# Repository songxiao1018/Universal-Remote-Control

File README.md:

# [Universal-Remote-Control](https://github.com/songxiao1018/Universal-Remote-Control)

本项目基于Arduino nano开发。采用KiCAD编辑器进行编辑

## 文件目录

| 编号 | 文件夹名        | 功能                     | 备注 |
| :--: | :------------: | :----------------------: | :--: |
| 1 | arduino-nano-data | Arduino nano 数据参考文件 |     |
| 2 | keyboard-nano     | KiCad 工程文件 |                |
| 3 | keyboard-code     | Arduino nano 软件程序部分 |  |

## 项目背景

本人在一次与家中长辈的聊天过程中偶然听到他们对于电视机遥控器的不满，他们对电视机遥控器有如下几个需求：

1. 遥控器操作简单，易于记忆。
2. 网络电视调台操作方便。
3. 遥控器按键已于操作，降低防误操作的发生。

本人在观察电视遥控器后也发现了这个问题的存在。因此，本人便想到了通过Arduino nano来实现一个通用遥控器，通过减少遥控器中的部分按键，集成化按键顺序等方法来解决遥控器操作不方便的问题。

## 项目目标

**基本**

- [x] 1. 实现遥控器基本功能。
- [x] 2. 方便老人使用。

**扩展**

- [ ] 3. 充放电自由，无需频繁更换换电池。
- [ ] 4. 小巧轻便，美丽外观。

## 项目进度

2023.01.10  V1.0a敲定成型，发往工厂制作样板

2022.12.28  项目开始

## 联系方式

- QQ：  2289895723
- Email：skyxiaoxiao@yeah.net
- Github：github.com/songxiao1018
- Blog：www.xiaoxiaosky.top

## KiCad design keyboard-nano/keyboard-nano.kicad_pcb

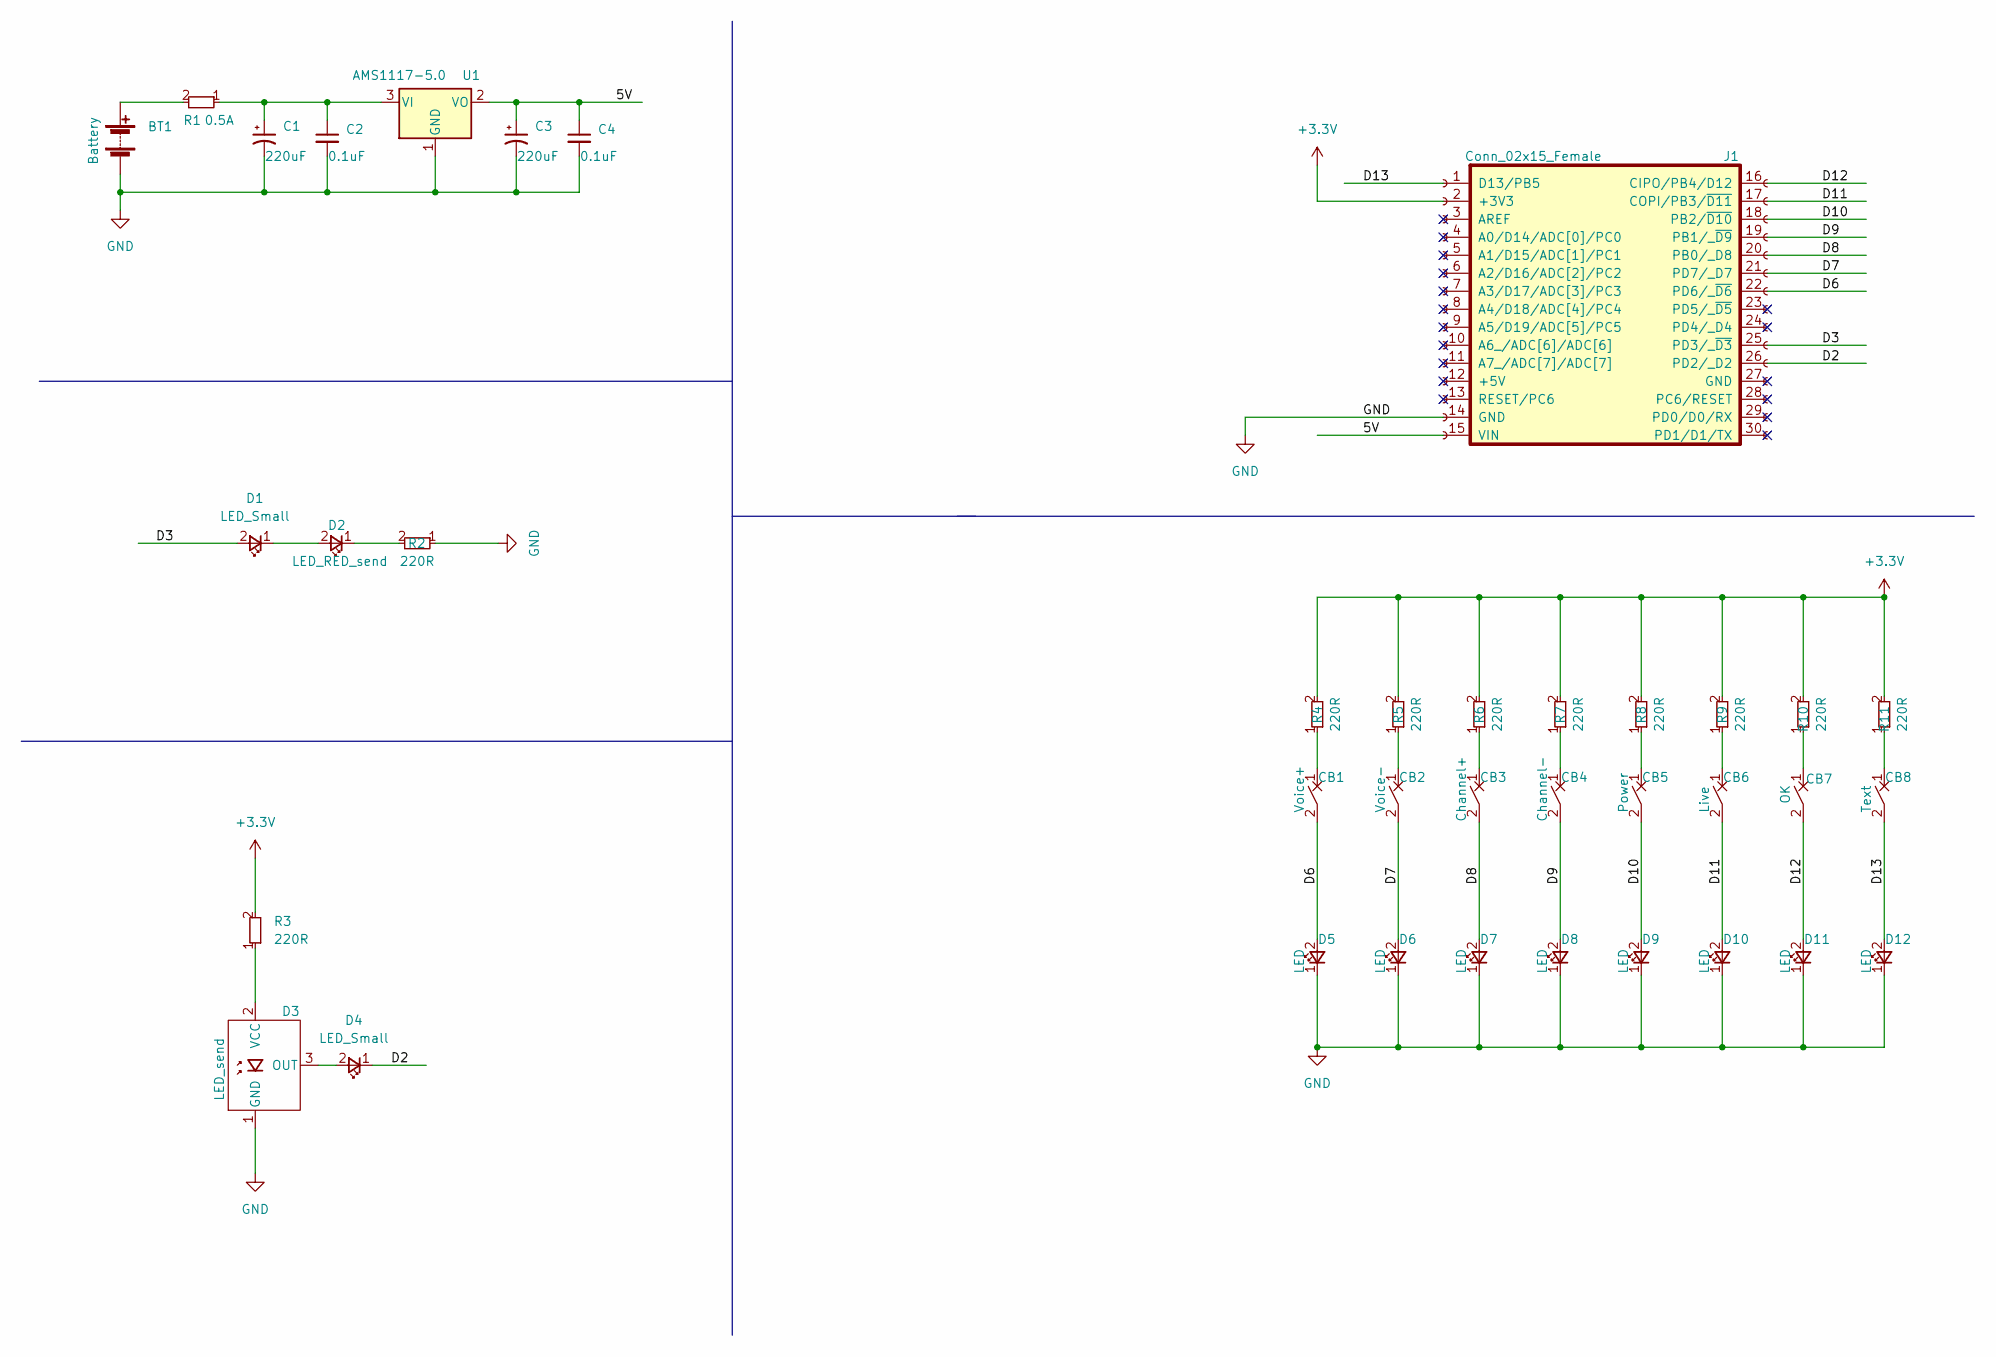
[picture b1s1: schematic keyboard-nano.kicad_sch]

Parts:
BT1: Battery; BatteryHolder_2xAAA_5
C1, C3: 220uF; C_Elec_6.3x7.7
C2, C4: 0.1uF; LED_0805_2012Metric
CB1: Voice+; SW_Cherry_MX_1.00u_Plate
CB2: Voice-; SW_Cherry_MX_1.00u_Plate
CB3: Channel+; SW_Cherry_MX_1.00u_Plate
CB4: Channel-; SW_Cherry_MX_1.00u_Plate
CB5: Power; SW_Cherry_MX_1.00u_Plate
CB6: Live; SW_Cherry_MX_1.00u_Plate
CB7: OK; SW_Cherry_MX_1.00u_Plate
CB8: Text; SW_Cherry_MX_1.00u_Plate
D1, D4: LED_Small; LED_0805_2012Metric
D2: LED_RED_send; Red_send
D3: LED_send; Red_get
D5, D6, D7, D8, D9, D10, D11, D12: LED; LED_0805_2012Metric
J1: Conn_02x15_Female; PinSocket_2x15_P2.54mm_nano
R1: 0.5A; LED_0805_2012Metric
R2, R3, R4, R5, R6, R7, R8, R9, R10, R11: 220R; LED_0805_2012Metric
U1: AMS1117-5.0; SOT-223-3_TabPin2

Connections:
+3.3V: J1.2 (+3V3), R3.2, R4.2, R5.2, R6.2, R7.2, R8.2, R9.2, R10.2, R11.2
/5V: C3.1, C4.1, J1.15 (VIN), U1.2 (VO)
/D2: D4.1 (K), J1.26 (PD2/_D2)
/D3: D1.2 (A), J1.25 (PD3/_~D3)
/D6: CB1.2, D5.2 (A), J1.22 (PD6/_~D6)
/D7: CB2.2, D6.2 (A), J1.21 (PD7/_D7)
/D8: CB3.2, D7.2 (A), J1.20 (PB0/_D8)
/D9: CB4.2, D8.2 (A), J1.19 (PB1/_~D9)
/D10: CB5.2, D9.2 (A), J1.18 (PB2/~D10)
/D11: CB6.2, D10.2 (A), J1.17 (COPI/PB3/~D11)
/D12: CB7.2, D11.2 (A), J1.16 (CIPO/PB4/D12)
/D13: CB8.2, D12.2 (A), J1.1 (D13/PB5)
GND: BT1.2 (-), C1.2, C2.2, C3.2, C4.2, D3.1 (GND), D5.1 (K), D6.1 (K), D7.1 (K), D8.1 (K), D9.1 (K), D10.1 (K), D11.1 (K), D12.1 (K), J1.14 (GND), R2.1, U1.1 (GND)
unnamed: BT1.1 (+), R1.2
unnamed: C1.1, C2.1, R1.1, U1.3 (VI)
unnamed: CB1.1, R4.1
unnamed: CB2.1, R5.1
unnamed: CB3.1, R6.1
unnamed: CB4.1, R7.1
unnamed: CB5.1, R8.1
unnamed: CB6.1, R9.1
unnamed: CB7.1, R10.1
unnamed: CB8.1, R11.1
unnamed: D1.1 (K), D2.2 (A)
unnamed: D2.1 (K), R2.2
unnamed: D3.2 (VCC), R3.1
unnamed: D3.3 (OUT), D4.2 (A)

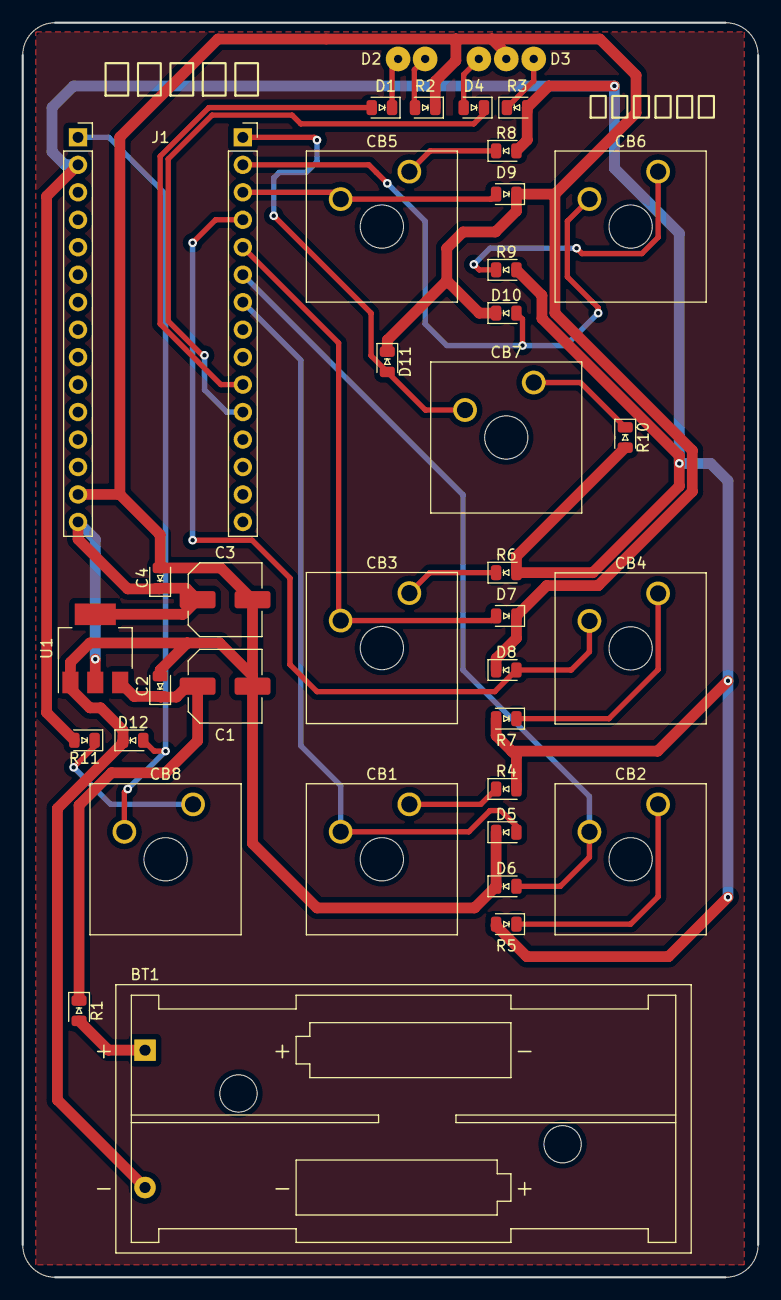
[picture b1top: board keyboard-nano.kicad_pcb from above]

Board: 2 copper layers, 68.0 x 116.0 mm, 38 parts (0 on the bottom side), 27 nets.

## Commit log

2023-01-10 V1.0a
2023-01-31 files
